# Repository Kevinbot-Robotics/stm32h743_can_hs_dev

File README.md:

# STM32H743 CAN + USB-HS Dev Board

An STM32H743 development board with on-board USB-HS and CAN-FD (up to 8Mbit/s)

## Documentation

Docs are available on [kevinbot.net](https://kevinbot.net/dev/stm32h743-can-hs/).
Documentation is licensed under the [CC BY-SA 4.0](https://creativecommons.org/licenses/by-sa/4.0/) license.

## Features

* STM32H743
* CAN-FD using DE-9 Industrial connector
* High Speed USB 2.0 using USB3300 ULPI PHY
* 128Mbit QuadSPI NOR flash
* SWD and JTAG debug using STDC14 Debug connector
* USB-C ports for DFU and HS
* Power path switching from HS and DFU port
* RGB LED
* Boot/Reset buttons

---

Prototypes for this project were sponsored by [PCBWay](https://www.pcbway.com/).

With their high-quality advanced PCB fabrication, fast turnaround, and excellent customer service, I recommend them for all of your PCB needs.

[Order online here, for as low at $5](https://www.pcbway.com/orderonline.aspx)

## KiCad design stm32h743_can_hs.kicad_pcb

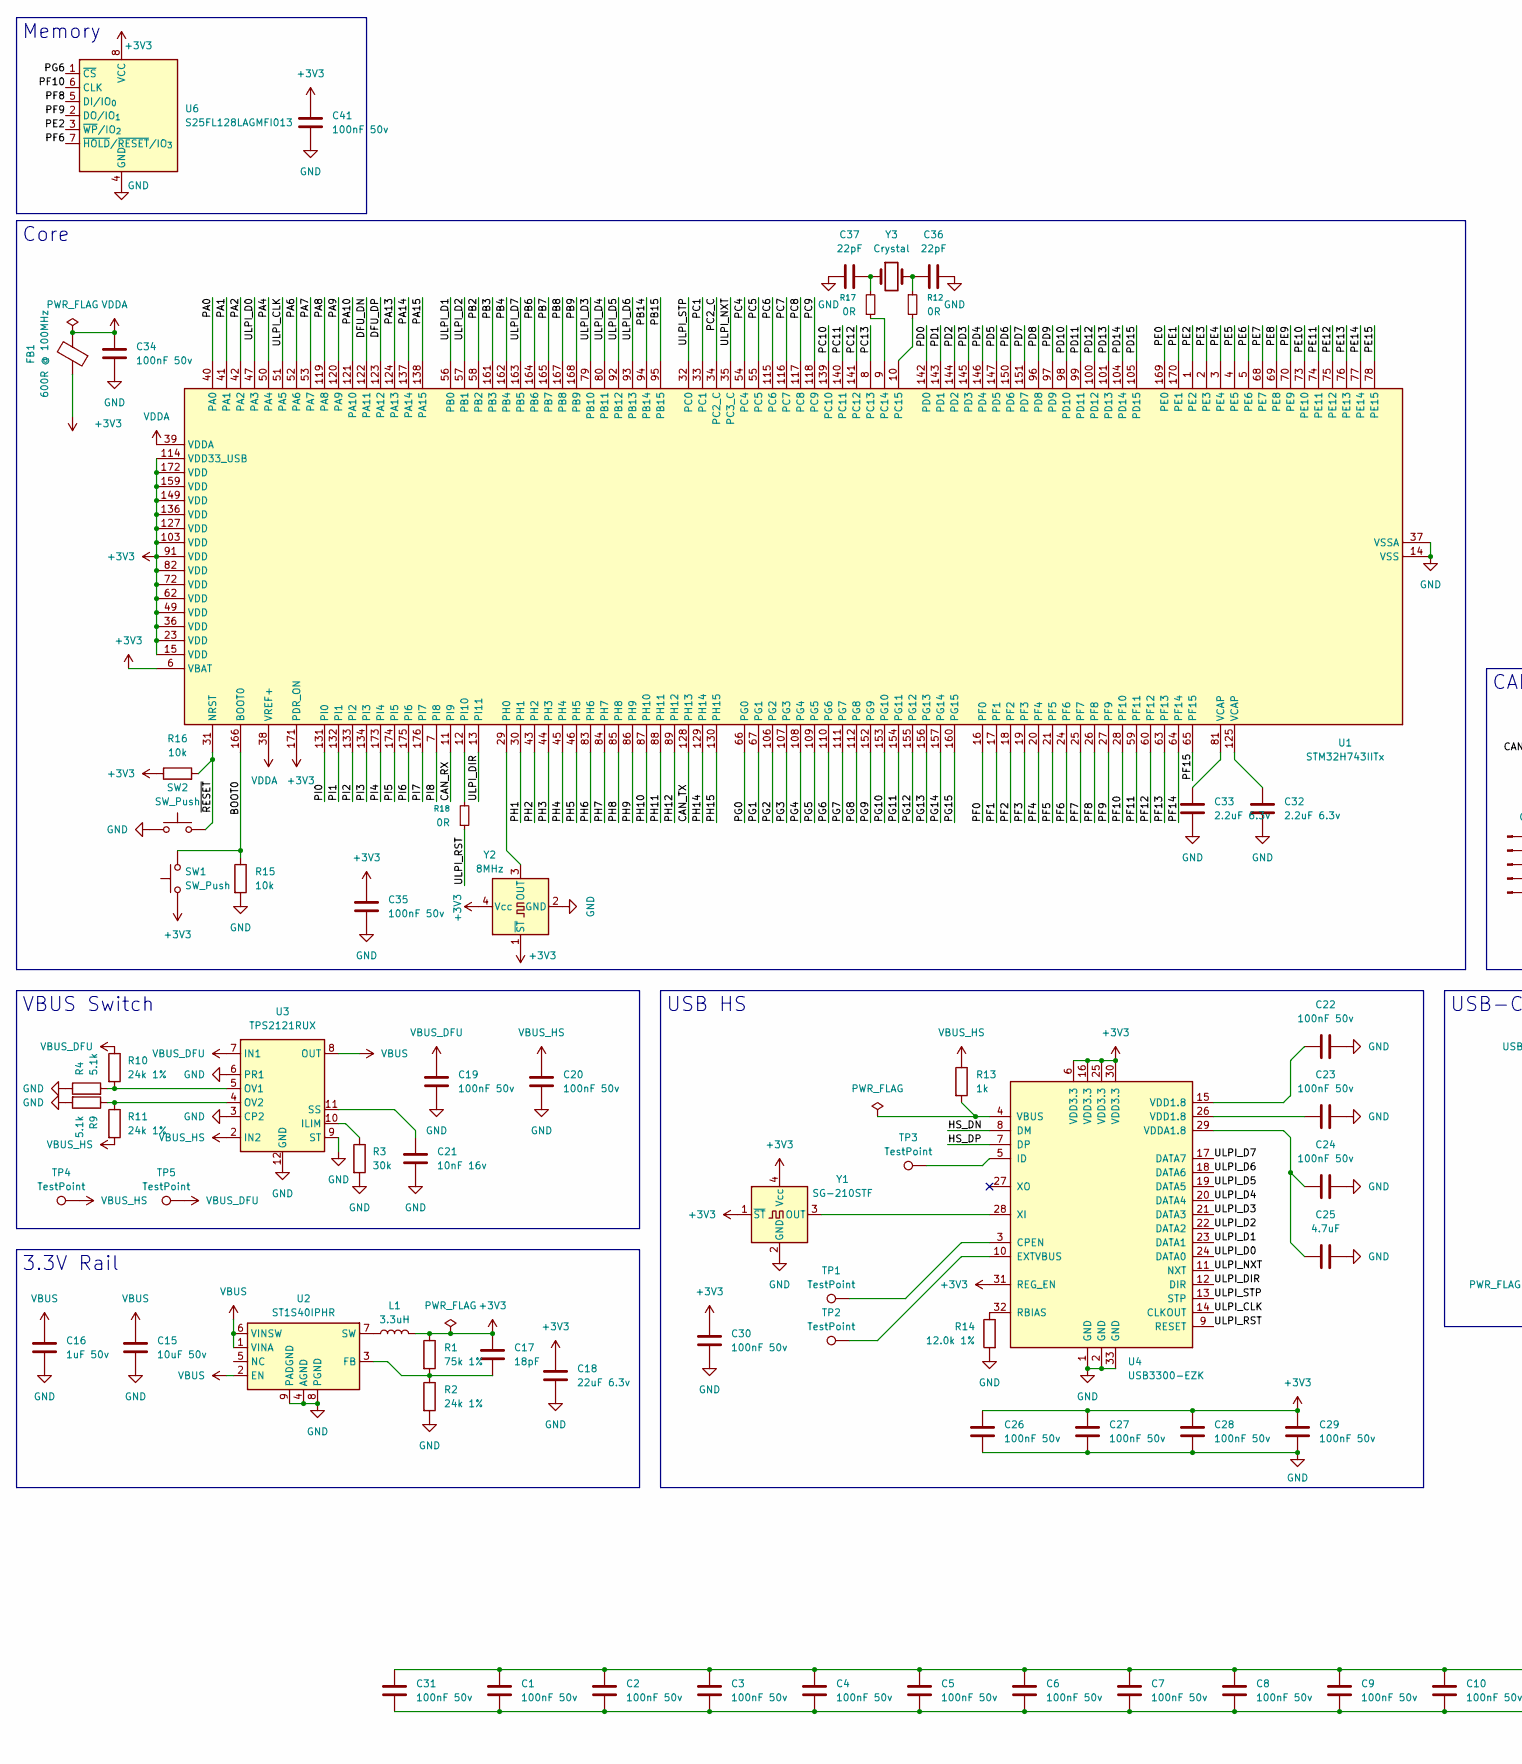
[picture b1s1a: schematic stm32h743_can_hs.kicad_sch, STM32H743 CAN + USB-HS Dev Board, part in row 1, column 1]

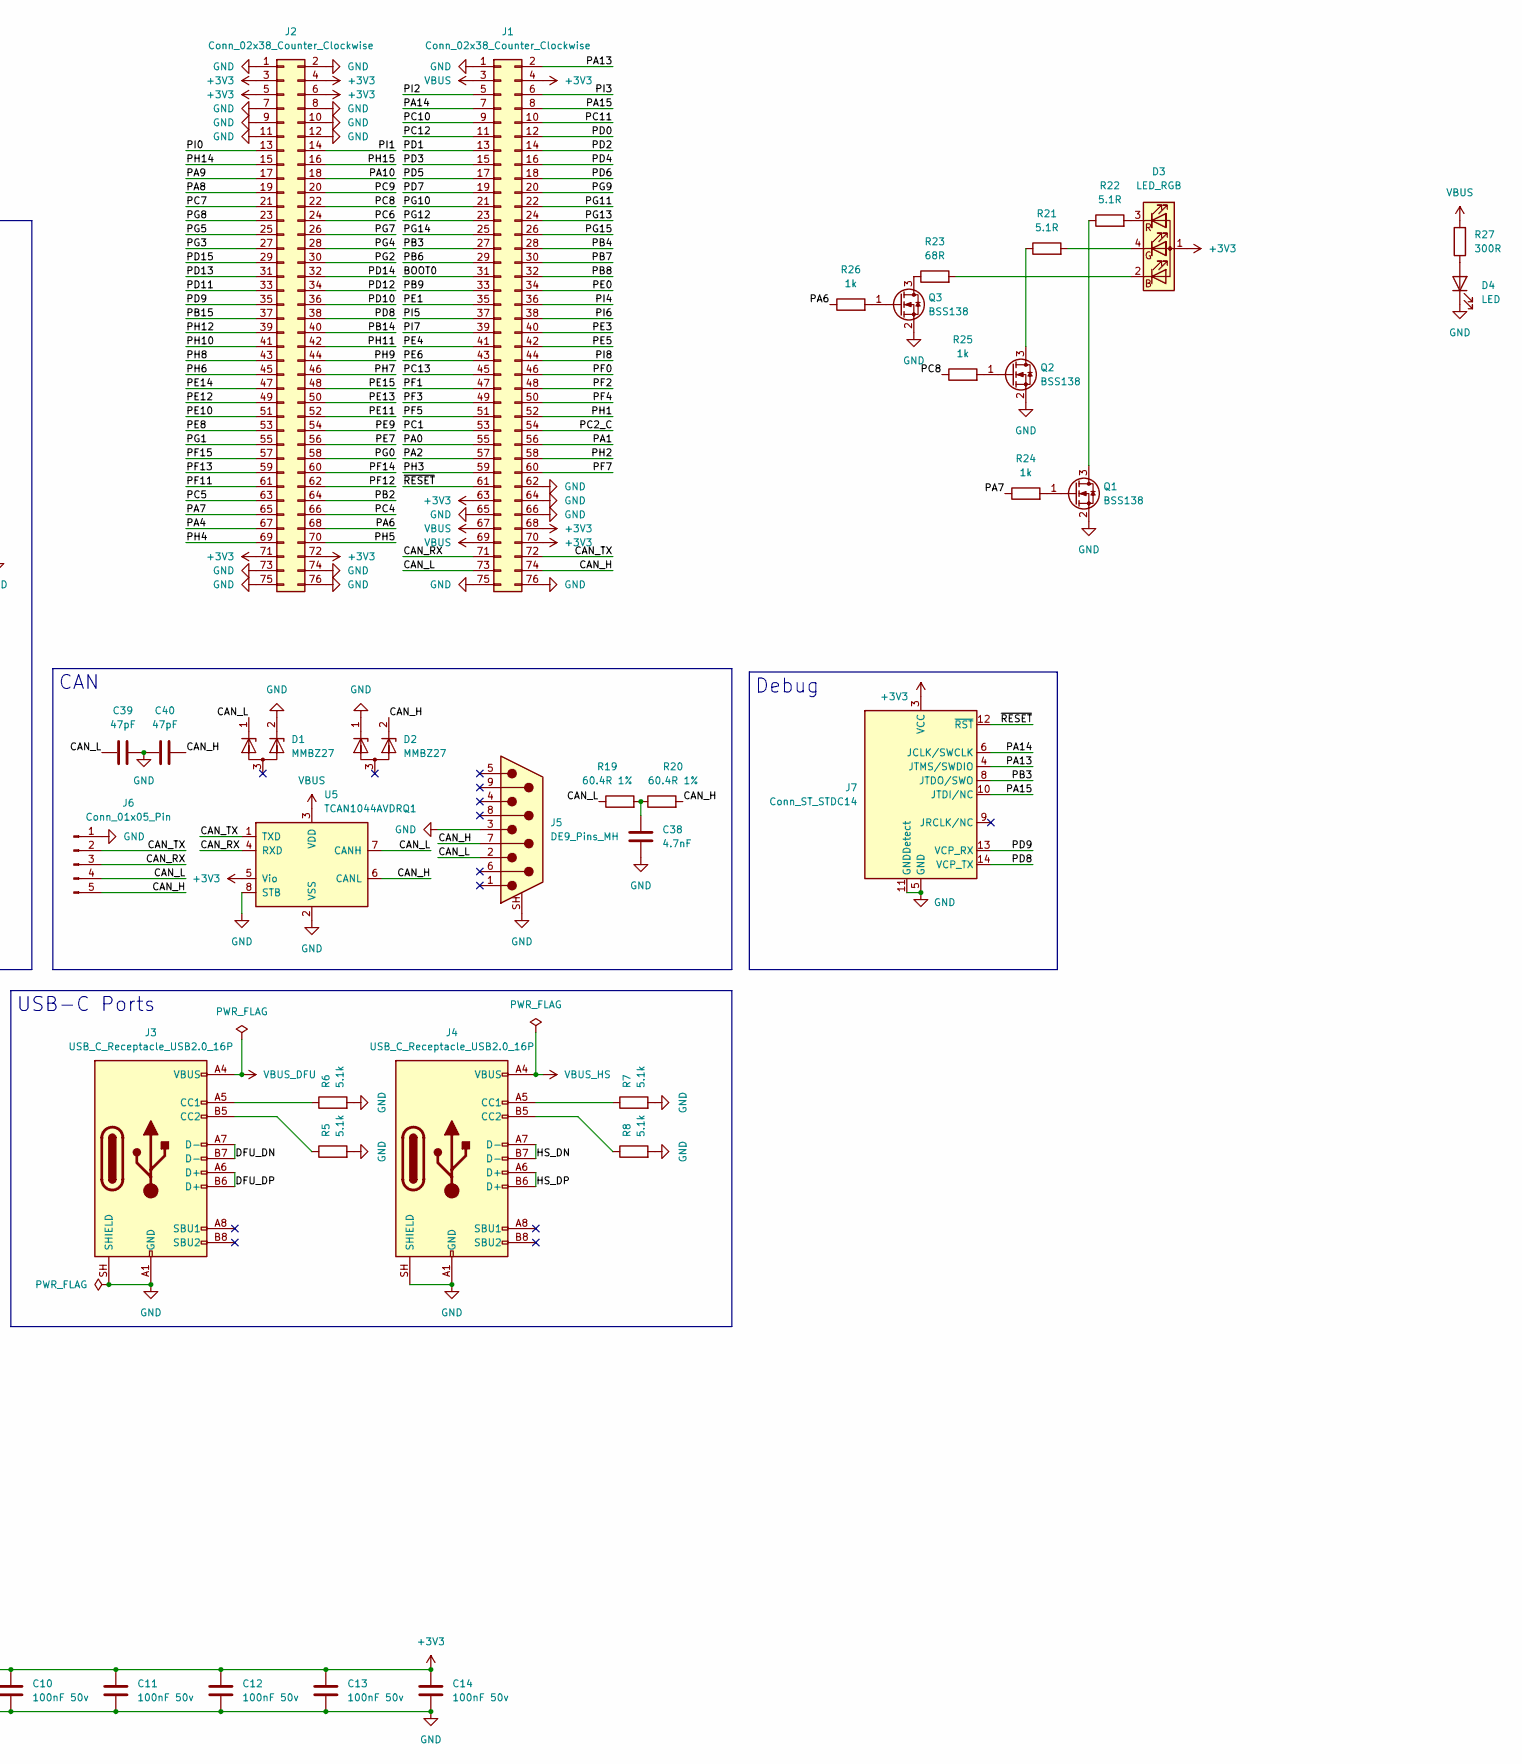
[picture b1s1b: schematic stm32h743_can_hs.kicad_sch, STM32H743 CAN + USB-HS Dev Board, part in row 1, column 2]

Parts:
C1, C2, C3, C4, C5, C6, C7, C8, C9, C10, C11, C12, C13, C14, C19, C20, C22, C23, C24, C26, C27, C28, C29, C30, C31, C34, C35, C41: 100nF 50v; C_0402_1005Metric
C15: 10uF 50v; C_0603_1608Metric
C16: 1uF 50v; C_0603_1608Metric
C17: 18pF; C_0402_1005Metric
C18: 22uF 6.3v; C_0603_1608Metric
C21: 10nF 16v; C_0402_1005Metric
C25: 4.7uF; C_0402_1005Metric
C32, C33: 2.2uF 6.3v; C_0402_1005Metric
C36, C37: 22pF; C_0402_1005Metric
C38: 4.7nF; C_0402_1005Metric
C39, C40: 47pF; C_0402_1005Metric
D1, D2: MMBZ27; SOT-23
D3: LED_RGB; LED_RGB_Wuerth-PLCC4_3.2x2.8mm_150141M173100
D4: LED; LED_0603_1608Metric
FB1: 600R @ 100MHz; L_0603_1608Metric
J1, J2: Conn_02x38_Counter_Clockwise; PinHeader_2x38_P2.54mm_Vertical
J3, J4: USB_C_Receptacle_USB2.0_16P; USB_C_Receptacle_GCT_USB4105-xx-A_16P_TopMnt_Horizontal
J5: DE9_Pins_MH; DSUB-9_Pins_Horizontal_P2.77x2.84mm_EdgePinOffset4.94mm_Hou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
J6: Conn_01x05_Pin; PinHeader_1x05_P2.54mm_Vertical
J7: Conn_ST_STDC14; SAMTEC_FTSH-107-01-X-DV-K
L1: 3.3uH; L_TDK_VLS6045EX_VLS6045AF
Q1, Q2, Q3: BSS138; SOT-323_SC-70
R1: 75k 1%; R_0402_1005Metric
R2, R10, R11: 24k 1%; R_0402_1005Metric
R3: 30k; R_0402_1005Metric
R4, R5, R6, R7, R8, R9: 5.1k; R_0402_1005Metric
R12, R17, R18: 0R; R_0402_1005Metric
R13, R24, R25, R26: 1k; R_0402_1005Metric
R14: 12.0k 1%; R_0402_1005Metric
R15, R16: 10k; R_0402_1005Metric
R19, R20: 60.4R 1%; R_0402_1005Metric
R21, R22: 5.1R; R_0402_1005Metric
R23: 68R; R_0402_1005Metric
R27: 300R; R_0402_1005Metric
SW1, SW2: SW_Push; SW_SPST_PTS810
TP1, TP2, TP3, TP4, TP5: TestPoint; TestPoint_Pad_D1.5mm
U1: STM32H743IITx; LQFP-176_24x24mm_P0.5mm
U2: ST1S40IPHR; TI_SO-PowerPAD-8
U3: TPS2121RUX; Texas_VQFN-HR-12_2x2.5mm_P0.5mm
U4: USB3300-EZK; QFN-32-1EP_5x5mm_P0.5mm_EP3.45x3.45mm
U5: TCAN1044AVDRQ1; SOIC-8_3.9x4.9mm_P1.27mm
U6: S25FL128LAGMFI013; SOIC-8_5.3x5.3mm_P1.27mm
Y1: SG-210STF; Oscillator_SMD_SeikoEpson_SG210-4Pin_2.5x2.0mm
Y2: 8MHz; Oscillator_SMD_SeikoEpson_SG210-4Pin_2.5x2.0mm
Y3: Crystal; Crystal_SMD_3215-2Pin_3.2x1.5mm

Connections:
+3V3: C1.1, C2.1, C3.1, C4.1, C5.1, C6.1, C7.1, C8.1, C9.1, C10.1, C11.1, C12.1, C13.1, C14.1, C17.1, C18.1, C26.1, C27.1, C28.1, C29.1, C30.1, C31.1, C35.1, C41.1, D3.1 (A), FB1.1, J1.4, J1.63, J1.68, J1.70, J2.3, J2.4, J2.5, J2.6, J2.71, J2.72, J7.3 (VCC), L1.2, R1.1, R16.1, SW1.1, U1.6 (VBAT), U1.15 (VDD), U1.23 (VDD), U1.36 (VDD), U1.49 (VDD), U1.62 (VDD), U1.72 (VDD), U1.82 (VDD), U1.91 (VDD), U1.103 (VDD), U1.114 (VDD33_USB), U1.127 (VDD), U1.136 (VDD), U1.149 (VDD), U1.159 (VDD), U1.171 (PDR_ON), U1.172 (VDD), U4.6 (VDD3.3), U4.16 (VDD3.3), U4.25 (VDD3.3), U4.30 (VDD3.3), U4.31 (REG_EN), U5.5 (Vio), U6.8 (VCC), Y1.1 (~ST), Y1.4 (Vcc), Y2.1 (~ST), Y2.4 (Vcc)
/BOOT0: J1.31, R15.1, SW1.2, U1.166 (BOOT0)
/CAN_H: C40.2, D2.2 (K), J1.74, J5.7, J6.5, R20.2, U5.6 (CANL)
/CAN_L: C39.1, D1.1 (K), J1.73, J5.2, J6.4, R19.1, U5.7 (CANH)
/CAN_RX: J1.71, J6.3, U1.11 (PI9), U5.4 (RXD)
/CAN_TX: J1.72, J6.2, U1.128 (PH13), U5.1 (TXD)
/DFU_DN: J3.A7 (D-), J3.B7 (D-), U1.122 (PA11)
/DFU_DP: J3.A6 (D+), J3.B6 (D+), U1.123 (PA12)
/HS_DN: J4.A7 (D-), J4.B7 (D-), U4.8 (DM)
/HS_DP: J4.A6 (D+), J4.B6 (D+), U4.7 (DP)
/PA0: J1.55, U1.40 (PA0)
/PA1: J1.56, U1.41 (PA1)
/PA2: J1.57, U1.42 (PA2)
/PA4: J2.67, U1.50 (PA4)
/PA6: J2.68, R26.1, U1.52 (PA6)
/PA7: J2.65, R24.1, U1.53 (PA7)
/PA8: J2.19, U1.119 (PA8)
/PA9: J2.17, U1.120 (PA9)
/PA10: J2.18, U1.121 (PA10)
/PA13: J1.2, J7.4 (JTMS/SWDIO), U1.124 (PA13)
/PA14: J1.7, J7.6 (JCLK/SWCLK), U1.137 (PA14)
/PA15: J1.8, J7.10 (JTDI/NC), U1.138 (PA15)
/PB2: J2.64, U1.58 (PB2)
/PB3: J1.27, J7.8 (JTDO/SWO), U1.161 (PB3)
/PB4: J1.28, U1.162 (PB4)
/PB6: J1.29, U1.164 (PB6)
/PB7: J1.30, U1.165 (PB7)
/PB8: J1.32, U1.167 (PB8)
/PB9: J1.33, U1.168 (PB9)
/PB14: J2.40, U1.94 (PB14)
/PB15: J2.37, U1.95 (PB15)
/PC1: J1.53, U1.33 (PC1)
/PC2_C: J1.54, U1.34 (PC2_C)
/PC4: J2.66, U1.54 (PC4)
/PC5: J2.63, U1.55 (PC5)
/PC6: J2.24, U1.115 (PC6)
/PC7: J2.21, U1.116 (PC7)
/PC8: J2.22, R25.1, U1.117 (PC8)
/PC9: J2.20, U1.118 (PC9)
/PC10: J1.9, U1.139 (PC10)
/PC11: J1.10, U1.140 (PC11)
/PC12: J1.11, U1.141 (PC12)
/PC13: J1.45, U1.8 (PC13)
/PD0: J1.12, U1.142 (PD0)
/PD1: J1.13, U1.143 (PD1)
/PD2: J1.14, U1.144 (PD2)
/PD3: J1.15, U1.145 (PD3)
/PD4: J1.16, U1.146 (PD4)
/PD5: J1.17, U1.147 (PD5)
/PD6: J1.18, U1.150 (PD6)
/PD7: J1.19, U1.151 (PD7)
/PD8: J2.38, J7.14 (VCP_TX), U1.96 (PD8)
/PD9: J2.35, J7.13 (VCP_RX), U1.97 (PD9)
/PD10: J2.36, U1.98 (PD10)
/PD11: J2.33, U1.99 (PD11)
/PD12: J2.34, U1.100 (PD12)
/PD13: J2.31, U1.101 (PD13)
/PD14: J2.32, U1.104 (PD14)
/PD15: J2.29, U1.105 (PD15)
/PE0: J1.34, U1.169 (PE0)
/PE1: J1.35, U1.170 (PE1)
/PE2: U1.1 (PE2), U6.3 (~WP/IO_{2})
/PE3: J1.40, U1.2 (PE3)
/PE4: J1.41, U1.3 (PE4)
/PE5: J1.42, U1.4 (PE5)
/PE6: J1.43, U1.5 (PE6)
/PE7: J2.56, U1.68 (PE7)
/PE8: J2.53, U1.69 (PE8)
/PE9: J2.54, U1.70 (PE9)
/PE10: J2.51, U1.73 (PE10)
/PE11: J2.52, U1.74 (PE11)
/PE12: J2.49, U1.75 (PE12)
/PE13: J2.50, U1.76 (PE13)
/PE14: J2.47, U1.77 (PE14)
/PE15: J2.48, U1.78 (PE15)
/PF0: J1.46, U1.16 (PF0)
/PF1: J1.47, U1.17 (PF1)
/PF2: J1.48, U1.18 (PF2)
/PF3: J1.49, U1.19 (PF3)
/PF4: J1.50, U1.20 (PF4)
/PF5: J1.51, U1.21 (PF5)
/PF6: U1.24 (PF6), U6.7 (~HOLD/~RESET/IO_{3})
/PF7: J1.60, U1.25 (PF7)
/PF8: U1.26 (PF8), U6.5 (DI/IO_{0})
/PF9: U1.27 (PF9), U6.2 (DO/IO_{1})
/PF10: U1.28 (PF10), U6.6 (CLK)
/PF11: J2.61, U1.59 (PF11)
/PF12: J2.62, U1.60 (PF12)
/PF13: J2.59, U1.63 (PF13)
/PF14: J2.60, U1.64 (PF14)
/PF15: J2.57, U1.65 (PF15)
/PG0: J2.58, U1.66 (PG0)
/PG1: J2.55, U1.67 (PG1)
/PG2: J2.30, U1.106 (PG2)
/PG3: J2.27, U1.107 (PG3)
/PG4: J2.28, U1.108 (PG4)
/PG5: J2.25, U1.109 (PG5)
/PG6: U1.110 (PG6), U6.1 (~CS)
/PG7: J2.26, U1.111 (PG7)
/PG8: J2.23, U1.112 (PG8)
/PG9: J1.20, U1.152 (PG9)
/PG10: J1.21, U1.153 (PG10)
/PG11: J1.22, U1.154 (PG11)
/PG12: J1.23, U1.155 (PG12)
/PG13: J1.24, U1.156 (PG13)
/PG14: J1.25, U1.157 (PG14)
/PG15: J1.26, U1.160 (PG15)
/PH1: J1.52, U1.30 (PH1)
/PH2: J1.58, U1.43 (PH2)
/PH3: J1.59, U1.44 (PH3)
/PH4: J2.69, U1.45 (PH4)
/PH5: J2.70, U1.46 (PH5)
/PH6: J2.45, U1.83 (PH6)
/PH7: J2.46, U1.84 (PH7)
/PH8: J2.43, U1.85 (PH8)
/PH9: J2.44, U1.86 (PH9)
/PH10: J2.41, U1.87 (PH10)
/PH11: J2.42, U1.88 (PH11)
/PH12: J2.39, U1.89 (PH12)
/PH14: J2.15, U1.129 (PH14)
/PH15: J2.16, U1.130 (PH15)
/PI0: J2.13, U1.131 (PI0)
/PI1: J2.14, U1.132 (PI1)
/PI2: J1.5, U1.133 (PI2)
/PI3: J1.6, U1.134 (PI3)
/PI4: J1.36, U1.173 (PI4)
/PI5: J1.37, U1.174 (PI5)
/PI6: J1.38, U1.175 (PI6)
/PI7: J1.39, U1.176 (PI7)
/PI8: J1.44, U1.7 (PI8)
/ULPI_CLK: U1.51 (PA5), U4.14 (CLKOUT)
/ULPI_D0: U1.47 (PA3), U4.24 (DATA0)
/ULPI_D1: U1.56 (PB0), U4.23 (DATA1)
/ULPI_D2: U1.57 (PB1), U4.22 (DATA2)
/ULPI_D3: U1.79 (PB10), U4.21 (DATA3)
/ULPI_D4: U1.80 (PB11), U4.20 (DATA4)
/ULPI_D5: U1.92 (PB12), U4.19 (DATA5)
/ULPI_D6: U1.93 (PB13), U4.18 (DATA6)
/ULPI_D7: U1.163 (PB5), U4.17 (DATA7)
/ULPI_DIR: U1.13 (PI11), U4.12 (DIR)
/ULPI_NXT: U1.35 (PC3_C), U4.11 (NXT)
/ULPI_RST: R18.1, U4.9 (RESET)
/ULPI_STP: U1.32 (PC0), U4.13 (STP)
/~RESET: J1.61, J7.12 (~RST), R16.2, SW2.2, U1.31 (NRST)
GND: C1.2, C2.2, C3.2, C4.2, C5.2, C6.2, C7.2, C8.2, C9.2, C10.2, C11.2, C12.2, C13.2, C14.2, C15.2, C16.2, C18.2, C19.2, C20.2, C21.2, C22.2, C23.2, C24.2, C25.2, C26.2, C27.2, C28.2, C29.2, C30.2, C31.2, C32.2, C33.2, C34.2, C35.2, C36.2, C37.1, C38.2, C39.2, C40.1, C41.2, D1.2 (K), D2.1 (K), D4.1 (K), J1.1, J1.62, J1.64, J1.65, J1.66, J1.75, J1.76, J2.1, J2.2, J2.7, J2.8, J2.9, J2.10, J2.11, J2.12, J2.73, J2.74, J2.75, J2.76, J3.A1 (GND), J3.A12 (GND), J3.B1 (GND), J3.B12 (GND), J3.SH (SHIELD), J4.A1 (GND), J4.A12 (GND), J4.B1 (GND), J4.B12 (GND), J4.SH (SHIELD), J5.3, J5.SH (PAD), J6.1, J7.5 (GND), J7.7 (GND), J7.11 (GNDDetect), Q1.2 (S), Q2.2 (S), Q3.2 (S), R2.2, R3.2, R4.1, R5.2, R6.2, R7.2, R8.2, R9.2, R14.2, R15.2, SW2.1, U1.14 (VSS), U1.22 (VSS), U1.37 (VSSA), U1.48 (VSS), U1.61 (VSS), U1.71 (VSS), U1.90 (VSS), U1.102 (VSS), U1.113 (VSS), U1.126 (VSS), U1.135 (VSS), U1.148 (VSS), U1.158 (VSS), U2.4 (AGND), U2.8 (PGND), U2.9 (PADGND), U3.3 (CP2), U3.6 (PR1), U3.9 (ST), U3.12 (GND), U4.1 (GND), U4.2 (GND), U4.33 (GND), U5.2 (VSS), U5.8 (STB), U6.4 (GND), Y1.2 (GND), Y2.2 (GND)
unnamed: C22.1, U4.15 (VDD1.8)
unnamed: C23.1, U4.26 (VDD1.8)
unnamed: C32.1, U1.125 (VCAP)
unnamed: C33.1, U1.81 (VCAP)
unnamed: C36.1, R12.1, Y3.2
unnamed: C37.2, R17.2, Y3.1
unnamed: C38.1, R19.2, R20.1
unnamed: D3.2 (BK), R23.2
unnamed: D3.4 (GK), R21.2
unnamed: D3.3 (RK), R22.2
unnamed: D4.2 (A), R27.1
unnamed: J3.A5 (CC1), R6.1
unnamed: J3.B5 (CC2), R5.1
unnamed: J4.A5 (CC1), R7.1
unnamed: J4.B5 (CC2), R8.1
unnamed: Q1.3 (D), R22.1
unnamed: Q1.1 (G), R24.2
unnamed: Q2.3 (D), R21.1
unnamed: Q2.1 (G), R25.2
unnamed: Q3.3 (D), R23.1
unnamed: Q3.1 (G), R26.2
unnamed: R17.1, U1.9 (PC14)
unnamed: R12.2, U1.10 (PC15)
unnamed: U1.29 (PH0), Y2.3 (OUT)
unnamed: R18.2, U1.12 (PI10)
unnamed: C17.2, R1.2, R2.1, U2.3 (FB)
unnamed: L1.1, U2.7 (SW)
unnamed: R3.1, U3.10 (ILIM)
unnamed: R4.2, R10.2, U3.5 (OV1)
unnamed: R9.1, R11.1, U3.4 (OV2)
unnamed: C21.1, U3.11 (SS)
unnamed: TP1.1 (1_1), U4.3 (CPEN)
unnamed: TP2.1 (1_1), U4.10 (EXTVBUS)
unnamed: TP3.1 (1_1), U4.5 (ID)
unnamed: R14.1, U4.32 (RBIAS)
unnamed: R13.2, U4.4 (VBUS)
unnamed: C24.1, C25.1, U4.29 (VDDA1.8)
unnamed: U4.28 (XI), Y1.3 (OUT)
VBUS: C15.1, C16.1, J1.3, J1.67, J1.69, R27.2, U2.1 (VINA), U2.2 (EN), U2.6 (VINSW), U3.1 (OUT), U3.8 (OUT), U5.3 (VDD)
VBUS_DFU: C19.1, J3.A4 (VBUS), J3.A9 (VBUS), J3.B4 (VBUS), J3.B9 (VBUS), R10.1, TP5.1 (1_1), U3.7 (IN1)
VBUS_HS: C20.1, J4.A4 (VBUS), J4.A9 (VBUS), J4.B4 (VBUS), J4.B9 (VBUS), R11.2, R13.1, TP4.1 (1_1), U3.2 (IN2)
VDDA: C34.1, FB1.2, U1.38 (VREF+), U1.39 (VDDA)

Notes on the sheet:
VBUS Switch
USB HS
Debug
Core
USB-C Ports
3.3V Rail
Memory
CAN

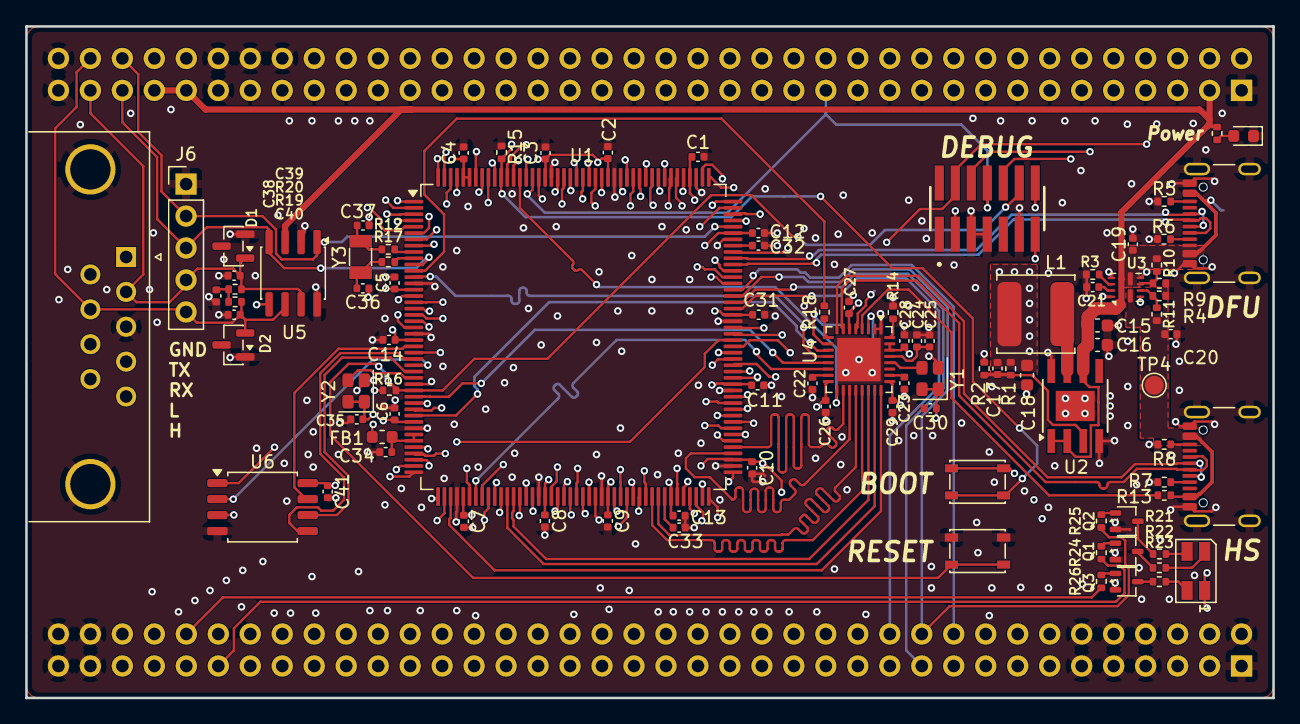
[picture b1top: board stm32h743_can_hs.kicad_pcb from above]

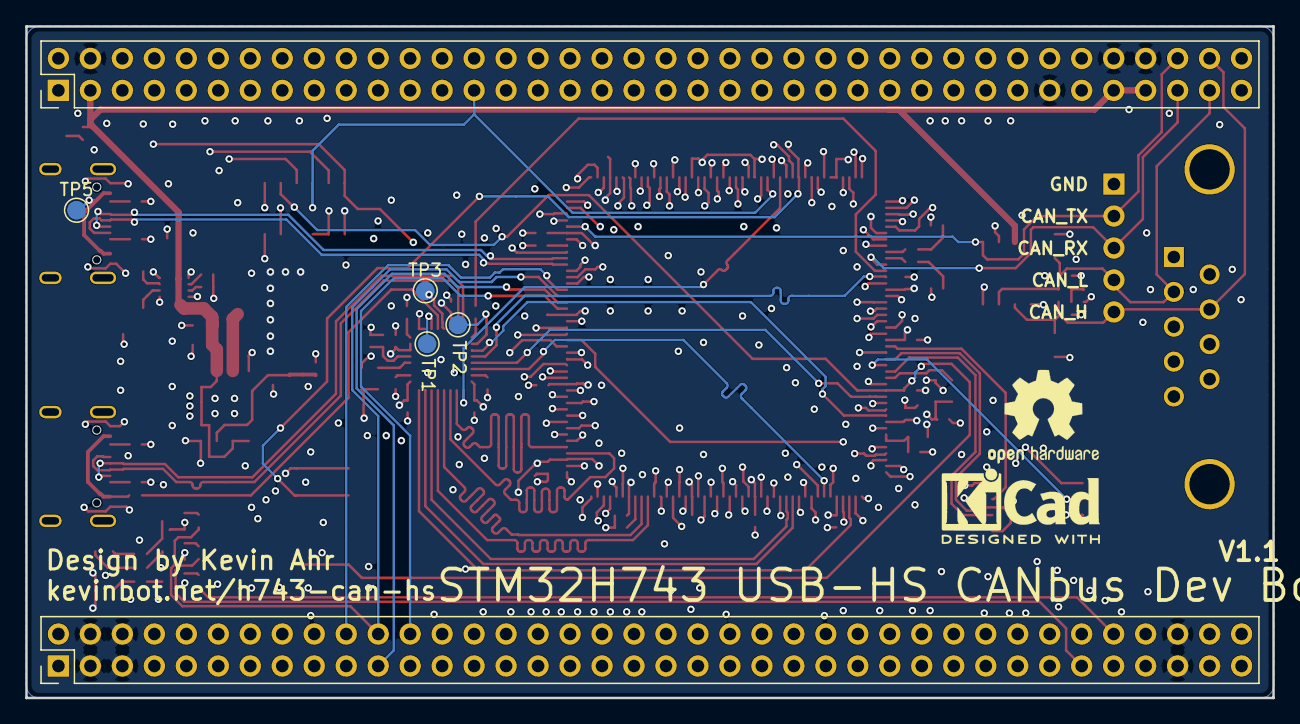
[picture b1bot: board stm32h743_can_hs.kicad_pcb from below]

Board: 4 copper layers, 99.1 x 53.3 mm, 102 parts (8 on the bottom side), 187 nets.

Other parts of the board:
GFX1: KiCad-Logo2_5mm_SilkScreen
GFX2: OSHW-Logo2_9.8x8mm_SilkScreen

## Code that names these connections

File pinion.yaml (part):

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                description: 'Ground'
                groups: ['ground']
            '2':
                name: PA13
                description: 'STM32 IO pin'
                groups: ['io']
            '3':
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                description: '3.3v Power, max 2A total'
                groups: ['power']
            '5':
                name: PI2
                description: 'STM32 IO pin'
                groups: ['io']
            '6':
                name: PI3
                description: 'STM32 IO pin'
                groups: ['io']
            '7':
                name: PA14
                description: 'STM32 IO pin'
                groups: ['io']
            '8':
                name: PA15
                description: 'STM32 IO pin'
                groups: ['io']
            '9':
                name: PC10
                description: 'STM32 IO pin'
                groups: ['io']
            '10':
                name: PC11
                description: 'STM32 IO pin'
                groups: ['io']
            '11':
                name: PC12
                description: 'STM32 IO pin'
                groups: ['io']
            '12':
                name: PD0
                description: 'STM32 IO pin'
                groups: ['io']
            '13':
                name: PD1
                description: 'STM32 IO pin'
                groups: ['io']
            '14':
                name: PD2
                description: 'STM32 IO pin'
                groups: ['io']
            '15':
                name: PD3
                description: 'STM32 IO pin'
                groups: ['io']
            '16':
                name: PD4
                description: 'STM32 IO pin'
                groups: ['io']
            '17':
                name: PD5
                description: 'STM32 IO pin'
                groups: ['io']
            '18':
                name: PD6
                description: 'STM32 IO pin'
                groups: ['io']
            '19':
                name: PD7
                description: 'STM32 IO pin'
                groups: ['io']
            '20':
                name: PG9
                description: 'STM32 IO pin'
                groups: ['io']
            '21':
                name: PG10
                description: 'STM32 IO pin'
                groups: ['io']
            '22':
                name: PG11
                description: 'STM32 IO pin'
                groups: ['io']
            '23':
                name: PG12
                description: 'STM32 IO pin'
                groups: ['io']
            '24':
                name: PG13
                description: 'STM32 IO pin'
                groups: ['io']
            '25':
                name: PG14
                description: 'STM32 IO pin'
                groups: ['io']
            '26':
                name: PG15
                description: 'STM32 IO pin'
                groups: ['io']
            '27':
                name: PB3
                description: 'STM32 IO pin'
                groups: ['io']
            '28':
                name: PB4
                description: 'STM32 IO pin'
                groups: ['io']
            '29':
                name: PB6
                description: 'STM32 IO pin'
                groups: ['io']
            '30':
                name: PB7
                description: 'STM32 IO pin'
                groups: ['io']
            '31':
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                description: 'Active-high Bootloader'
                groups: ['core']
            '32':
                name: PB8
                description: 'STM32 IO pin'
                groups: ['io']
            '33':
                name: PB9
                description: 'STM32 IO pin'
                groups: ['io']
            '34':
                name: PE0
                description: 'STM32 IO pin'
                groups: ['io']
            '35':
                name: PE1
                description: 'STM32 IO pin'
                groups: ['io']
            '36':
                name: PI4
                description: 'STM32 IO pin'
                groups: ['io']
            '37':
                name: PI5
                description: 'STM32 IO pin'
                groups: ['io']
            '38':
                name: PI6
                description: 'STM32 IO pin'
                groups: ['io']
            '39':
                name: PI7
                description: 'STM32 IO pin'
                groups: ['io']
            '40':
                name: PE3
                description: 'STM32 IO pin'
                groups: ['io']
            '41':
                name: PE4
                description: 'STM32 IO pin'
                groups: ['io']
            '42':
                name: PE5
                description: 'STM32 IO pin'
                groups: ['io']
            '43':
                name: PE6
                description: 'STM32 IO pin'
                groups: ['io']
            '44':
                name: PI8
                description: 'STM32 IO pin'
                groups: ['io']
            '45':
                name: PC13
                description: 'STM32 IO pin'
                groups: ['io']
            '46':
                name: PF0
                description: 'STM32 IO pin'
                groups: ['io']
            '47':
                name: PF1
                description: 'STM32 IO pin'
                groups: ['io']
            '48':
                name: PF2
                description: 'STM32 IO pin'
                groups: ['io']
            '49':
                name: PF3
                description: 'STM32 IO pin'
                groups: ['io']
            '50':
                name: PF4
                description: 'STM32 IO pin'
                groups: ['io']
            '51':
                name: PF5
                description: 'STM32 IO pin'
                groups: ['io']
            '52':
                name: PH1
                description: 'STM32 IO pin'
                groups: ['io']
            '53':
                name: PC1
                description: 'STM32 IO pin'
                groups: ['io']
            '54':
                name: PC2_C
                description: 'STM32 IO pin'
                groups: ['io']
            '55':
                name: PA0
                description: 'STM32 IO pin'
                groups: ['io']
            '56':
                name: PA1
                description: 'STM32 IO pin'
                groups: ['io']
            '57':
                name: PA2
                description: 'STM32 IO pin'
                groups: ['io']
            '58':
                name: PH2
                description: 'STM32 IO pin'
                groups: ['io']
            '59':
                name: PH3
                description: 'STM32 IO pin'
                groups: ['io']
            '60':
                name: PF7
                description: 'STM32 IO pin'
                groups: ['io']
            '61':
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                groups: ['power']
            '71':
                name: CAN_RX
                description: 'CANbus transciever RX, PI9'
                groups: ['io']
            '72':
                name: CAN_TX
                description: 'CANbus transciever TX, PH13'
                groups: ['io']
            '73':
                name: CAN_L
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                description: 'Ground'
                groups: ['ground']
            '13':
                name: PI0
                description: 'STM32 IO pin'
                groups: ['io']
            '14':
                name: PI1
                description: 'STM32 IO pin'
                groups: ['io']
            '15':
                name: PH14
                description: 'STM32 IO pin'
                groups: ['io']
            '16':
                name: PH15
                description: 'STM32 IO pin'
                groups: ['io']
            '17':
                name: PA9
                description: 'STM32 IO pin'
                groups: ['io']
            '18':
                name: PA10
                description: 'STM32 IO pin'
                groups: ['io']
            '19':
                name: PA8
                description: 'STM32 IO pin'
                groups: ['io']
            '20':
                name: PC9
                description: 'STM32 IO pin'
                groups: ['io']
            '21':
                name: PC7
                description: 'STM32 IO pin'
                groups: ['io']
            '22':
                name: PC8
                description: 'STM32 IO pin'
                groups: ['io']
            '23':
                name: PG8
                description: 'STM32 IO pin'
                groups: ['io']
            '24':
                name: PC6
                description: 'STM32 IO pin'
                groups: ['io']
            '25':
                name: PG5
                description: 'STM32 IO pin'
                groups: ['io']
            '26':
                name: PG7
                description: 'STM32 IO pin'
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
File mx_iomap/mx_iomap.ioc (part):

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Mcu.Name=STM32H743IITx
Mcu.Package=LQFP176
Mcu.UserName=STM32H743IITx
PA11.Mode=Device_Only
PA11.Signal=USB_OTG_FS_DM
PA12.Mode=Device_Only
PA12.Signal=USB_OTG_FS_DP
PA13\ (JTMS/SWDIO).Mode=Trace_Asynchronous_SW
PA13\ (JTMS/SWDIO).Signal=DEBUG_JTMS-SWDIO
PA14\ (JTCK/SWCLK).Mode=Trace_Asynchronous_SW
PA14\ (JTCK/SWCLK).Signal=DEBUG_JTCK-SWCLK
PA3.Mode=Device_HS
PA3.Signal=USB_OTG_HS_ULPI_D0
PA5.Mode=Device_HS
PA5.Signal=USB_OTG_HS_ULPI_CK
PA6.GPIOParameters=GPIO_Label
PA6.GPIO_Label=RGB RED
PA6.Signal=S_TIM3_CH1
PA7.GPIOParameters=GPIO_Label
PA7.GPIO_Label=RGB GREEN
PA7.Signal=S_TIM3_CH2
PB0.Mode=Device_HS
PB0.Signal=USB_OTG_HS_ULPI_D1
PB1.Mode=Device_HS
PB1.Signal=USB_OTG_HS_ULPI_D2
PB10.Mode=Device_HS
PB10.Signal=USB_OTG_HS_ULPI_D3
PB11.Mode=Device_HS
PB11.Signal=USB_OTG_HS_ULPI_D4
PB12.Mode=Device_HS
PB12.Signal=USB_OTG_HS_ULPI_D5
PB13.Mode=Device_HS
PB13.Signal=USB_OTG_HS_ULPI_D6
PB3\ (JTDO/TRACESWO).Mode=Trace_Asynchronous_SW
PB3\ (JTDO/TRACESWO).Signal=DEBUG_JTDO-SWO
PB5.Mode=Device_HS
PB5.Signal=USB_OTG_HS_ULPI_D7
PC0.Mode=Device_HS
PC0.Signal=USB_OTG_HS_ULPI_STP
PC14-OSC32_IN\ (OSC32_IN).Mode=LSE-External-Oscillator
PC14-OSC32_IN\ (OSC32_IN).Signal=RCC_OSC32_IN
PC15-OSC32_OUT\ (OSC32_OUT).Mode=LSE-External-Oscillator
PC15-OSC32_OUT\ (OSC32_OUT).Signal=RCC_OSC32_OUT
PC3_C.Mode=Device_HS
PC3_C.Signal=USB_OTG_HS_ULPI_NXT
PC8.GPIOParameters=GPIO_Label
PC8.GPIO_Label=RGB BLUE
PC8.Signal=S_TIM3_CH3
PE2.Mode=Single Bank 1
PE2.Signal=QUADSPI_BK1_IO2
PF10.Mode=Single Bank 1
PF10.Signal=QUADSPI_CLK
PF6.Mode=Single Bank 1
PF6.Signal=QUADSPI_BK1_IO3
PF8.Mode=Single Bank 1
PF8.Signal=QUADSPI_BK1_IO0
PF9.Mode=Single Bank 1
PF9.Signal=QUADSPI_BK1_IO1
PG6.Mode=Single Bank 1
PG6.Signal=QUADSPI_BK1_NCS
PH0-OSC_IN\ (PH0).Mode=HSE-External-Clock-Source
PH0-OSC_IN\ (PH0).Signal=RCC_OSC_IN
PH13.Mode=FDCAN_Activate
PH13.Signal=FDCAN1_TX
PI11.Mode=Device_HS
PI11.Signal=USB_OTG_HS_ULPI_DIR
PI9.Mode=FDCAN_Activate
PI9.Signal=FDCAN1_RX
RCC.HSE_VALUE=8000000
RCC.SYSCLKFreq_VALUE=64000000
board=custom

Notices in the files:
stm32h743_can_hs.kicad_pcb:
Licensed under the GNU GPL-3.0
